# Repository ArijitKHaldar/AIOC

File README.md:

# AIOC-BMT

This is the Ham Radio _All-in-one-Cable_ with a USB Type-A instead of USB-C which is inspired from [AIOC](https://github.com/skuep/AIOC). **It is currently not tested, and is still a proof of concept only!** Please read this README carefully before ordering anything.

## What does it do?

The AIOC-BMT is a small adapter with a USB-A connector that enumerates itself as a sound-card (e.g. for APRS purposes), a virtual tty ("COM Port") for programming and asserting the PTT (Push-To-Talk) as well as a CM108 compatible HID endpoint for CM108-style PTT (new in firmware version 1.2.0).

## Features

- Cheap & Hackable Digital mode USB interface (similar to digirig, mobilinkd, etc...)
- Programming Cable Function via virtual Serial Port
- Compact form-factor (DIY overmolded enclosure is currently TBD)
- Based on easy-to-hack **STM32F302** with internal ADC/DAC (Programmable via USB bootloader using [DFU](#how-to-program))
- Can support Dual-PTT HTs
- Supports all popular OSes (Linux, Windows and MacOS with limitations[\*](https://github.com/skuep/AIOC/issues/13))

## Compatibility

### Software

- [Direwolf](#notes-on-direwolf) as AX.25 modem/APRS en+decoder/...
- [AllStarLink](#notes-on-allstarlink-asl3) as ASL Node
- [APRSdroid](#notes-on-aprsdroid) as APRS en+decoder
- [CHIRP](#notes-on-chirp) for programming
- [VaraFM](#notes-on-varafm)
- ... and more

### Tested Radios (so far)

TODO

## How To Fab

- Go to JLCPCB.com and upload the AIOC-BMT.zip package (under `aioc-bmt\production`)
  - Select PCB Thickness 1.6mm (you can select any thickness of your choice, as long as the USB connector can be mounted)
  - You may want to select LeadFree HASL
  - Select Silkscreen/Soldermask color to your liking
  - Choose Mark on PCB: Order Number(Specify Position)
- Check "PCB Assembly"
  - PCBA Type "Economic"
  - Assembly Side "Top Side"
  - Tooling Holes "Added by Customer"
  - Press Confirm
  - Click "Add BOM File" and upload `bom.csv`
  - Click "Add CPL File" and upload `positions.csv`
  - Press Next
  - Look Through components, see if something is missing or problematic and press Next
  - Check everything looks roughly good (rotations are already baked-in and should be correct). Save to Cart

This gives you 5 (or more) SMD assembled AIOC-BMT. The only thing left to do is soldering on the audio cables.
You can choose to fabricate 5 PCBs, but populate 2, which will reduce the cost, but you have to solder the rest of the boards yourself in that case.

**Note** that the following message from JLCPCB is okay and can be ignored.

```
The below parts won't be assembled due to data missing.
J1,J2,J3,J4 designators don't exist in the BOM file.
```

**Note** for people doing their own PCB production: I suggest using the LCSC part numbers in the BOM file as a guide on what to buy (especially regarding the MCU).

## How To Build

For building the firmware, clone the repository and initialize the submodules. Create an empty workspace with the STM32CubeIDE and import the project.

- `git clone <repositry url>`
- `git submodule update --init`
- Start STM32CubeIDE and create a new workspace under `<project-root>/stm32`
- Choose File->Import and import the `aioc-fw` project in the same folder without copying
- Select Project->Build All and the project should build. Use the Release build unless you specifically want to debug an issue

## How To Program

### Initial programming

The following steps are required for initial programming of the AIOC-BMT:

- Short outermost pins on the programming header. This will set the device into bootloader mode in the next step.
  
- Connect USB-A cable to the AIOC-BMT PCB
- Use a tool like `dfu-util` to program the firmware binary from the GitHub Releases page like this:
  ```
  dfu-util -a 0 -s 0x08000000:leave -D aioc-fw-x-y-z.bin
  ```
  **Note** that a `libusb` driver is required for this. On Windows there are additional steps required as shown [here](https://yeswolf.github.io/dfu) (_DFuSe Utility and dfu-util_). On other operating systems (e.g. Linux, MacOS), this just works ™ (provided libusb is installed on your system).
  On Linux (and MacOS), your user either needs to have the permission to use libusb (`plugdev` group) or you might need to use `sudo`.
- Remove short from first step, unplug and replug the device, it should now enumerate as the AIOC-BMT device

### Firmware updating

Once the AIOC-BMT has firmware loaded onto it, it can be re-programmed without the above BOOT sequence by following these steps.

**Note** This requires firmware version >= 1.2.0. For older firmwares, the initial programming sequence above is required for updating the firmware.

- Run `dfu-util` like this
  ```
  dfu-util -d 1209:7388 -a 0 -s 0x08000000:leave -D aioc-fw-x-y-z.bin
  ```

This will reboot the AIOC-BMT into the bootloader automatically and perform the programming.
After that, it automatically reboots the AIOC-BMT into the newly programmed firmware.

**Note** Should you find yourself with a bricked AIOC-BMT, use the initial programming sequence above

## How To Use

The serial interface of the AIOC-BMT enumerates as a regular COM (Windows) or ttyACM port (Linux) and can be used as such for programming the radio as well as PTT (Asserted on `DTR=1` and `RTS=0`).

**Note** before firmware version 1.2.0, PTT was asserted by `DTR=1` (ignoring RTS) which caused problems with certain radios when using the serial port for programming the radio e.g. using CHIRP.

The soundcard interface of the AIOC-BMT gives access to the audio data channels. It has one mono microphone channel and one mono speaker channel and currently supports the following baudrates:

- 48000 Hz (preferred)
- 32000 Hz
- 24000 Hz
- 22050 Hz (specifically for APRSdroid, has approx. 90 ppm of frequency error)
- 16000 Hz
- 12000 Hz
- 11025 Hz (has approx. 90 ppm of frequency error)
- 8000 Hz

Since firmware version 1.2.0, a CM108 style PTT interface is available for public testing. This interface works in parallel to the COM-port PTT.
Direwolf on Linux is confirmed working, please report any issues. Note that currently, Direwolf reports some warnings when using the CM108 PTT interface on the AIOC.
While they are annoying, they are safe to ignore and require changes in the upstream direwolf sourcecode. See https://github.com/wb2osz/direwolf/issues/448 for more details.

## Notes on Direwolf

- Follow the regular setup guide with [Direwolf](https://github.com/wb2osz/direwolf) to determine the correct audio device to use.
  For the serial and CM108 PTT interfaces on Linux, you need to set correct permissions on the ttyACM/hidraw devices. Consult Direwolf manual.
- Configure the device as follows
  ```
  [...]
  ADEVICE plughw:<x>,0  # <- Linux
  ADEVICE x 0           # <- Windows
  ARATE 48000
  [...]
  PTT CM108             # <- Use the new CM108 compatible style PTT interface
  PTT <port> DTR -RTS   # <- Alternatively use an old school serial device for PTT
  [...]
  ```

## Notes on AllStarLink (ASL3)

Once your cable is emulating a CM108, it becomes quite simple to plug into your HT and setup a simple simplex AllStarLink node that talks to your favorite repeater or node.

In `asl-menu`, set:

- Device type: `usbradio` (menu sections: 2 > A1 > N4 > I2)
- Duplex type: `1` (menu sections: 2 > A1 > N5)

Edit `usbradio.conf` (menu sections: 6 > H) (for a Puxing PX-888 cheap Chineese HT)

- `rxboost = 0`
- `rxsqhyst = 500`
- `carrierfrom = usbinvert`
- `ctcssfrom = no`
- `rxdemod = speaker`
- `txprelim = no`
- `invertptt = no`

## Notes on APRSdroid

[APRSdroid](https://aprsdroid.org/) support has been added by AIOC by implementing support for the fixed 22050 Hz sample rate that APRSdroid requires.
It is important to notice, that the exact sample rate can not be achieved by the hardware, due to the 8 MHz crystal.
The actual sample rate used is 22052 Hz (which represents around 90 ppm of error). From my testing this does not seem to be a problem for APRS at all.

However, since APRSdroid does not have any PTT control, sending data is currently not possible using the AIOC except using the radio VOX function. See https://github.com/ge0rg/aprsdroid/issues/324.
My previous experience is, that the Android kernel brings support for ttyACM devices (which is perfect for the AIOC) so implementing this feature for APRSdroid should theoretically be no problem.

Ideas such as implementing a digital-modes-spefic VOX-emulation to workaround this problem and let the AIOC activate the PTT automatically are currently being considered.
Voice your opinion and ideas in the GitHub issues if this seems interesting to you.

## Notes on CHIRP

CHIRP is a very popuplar open-source programming software that supports a very wide array of HT radios. You can use CHIRP just as you would like with a regular programming cable.

Download:

- Start CHIRP
- Select Radio->Download from Radio
- Select the AIOC COM/ttyACM port and start

Upload:

- Select Radio->Upload to Radio
- That's it

## Notes on VaraFM

Select "DTR only" for PTT Pin, so that the correct RTS/DTR sequence is generated for PTT

# Known issues

TODO

# Future work

TODO

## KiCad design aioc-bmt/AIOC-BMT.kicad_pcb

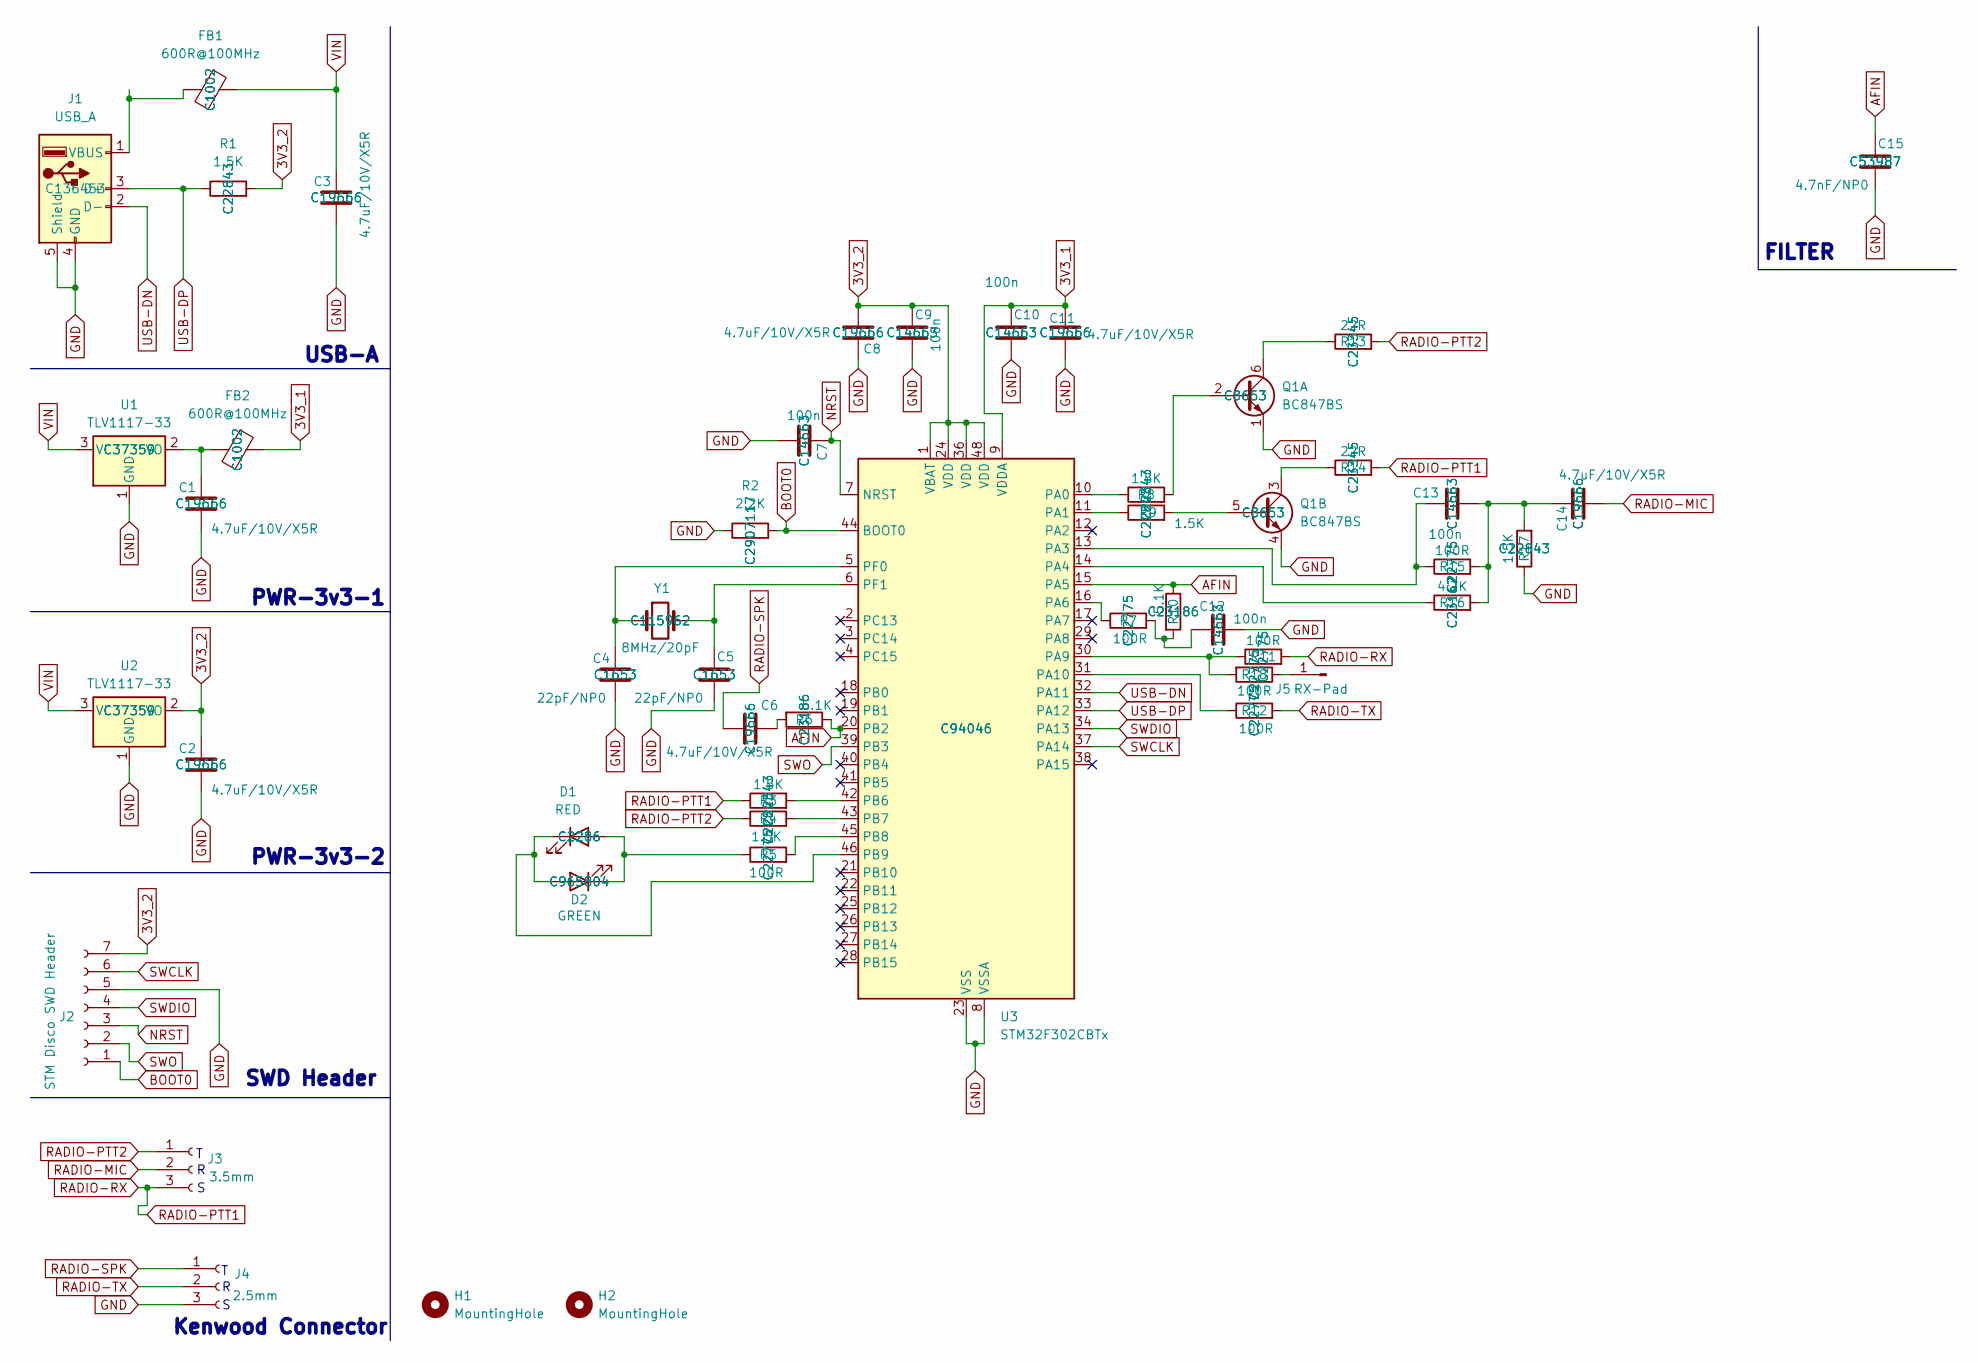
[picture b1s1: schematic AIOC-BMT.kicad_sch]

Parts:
C1, C2, C3, C6, C8, C11, C14: 4.7uF/10V/X5R; C_0603_1608Metric_Pad1.08x0.95mm_HandSolder; MPN C19666; LCSC Part# C19666
C4, C5: 22pF/NP0; C_0603_1608Metric_Pad1.08x0.95mm_HandSolder; MPN C1653; LCSC Part# C1653
C7, C9, C10, C12, C13: 100n; C_0603_1608Metric_Pad1.08x0.95mm_HandSolder; MPN C14663; LCSC Part# C14663
C15: 4.7nF/NP0; C_0603_1608Metric_Pad1.08x0.95mm_HandSolder; MPN C53987; LCSC Part# C53987
D1: RED; LED_0603_1608Metric_Pad1.05x0.95mm_HandSolder; MPN C2286; LCSC Part# C2286
D2: GREEN; LED_0603_1608Metric_Pad1.05x0.95mm_HandSolder; MPN C965804; LCSC Part# C965804
FB1, FB2: 600R@100MHz; L_0603_1608Metric_Pad1.05x0.95mm_HandSolder; MPN C1002; LCSC Part# C1002
H1, H2: MountingHole; ToolingHole_1.152mm
J1: USB_A; USB_A_Molex_48037-2200_Horizontal; MPN C136453; LCSC Part# C136453
J2: STM Disco SWD Header; PinSocket_1x07_P2.54mm_Vertical
J3: 3.5mm; PinSocket_1x03_P2.54mm_Vertical
J4: 2.5mm; PinSocket_1x03_P2.54mm_Vertical
J5: RX-Pad; TestPoint_Pad_2.5x2.5mm
Q1: BC847BS; SOT-363_SC-70-6; MPN C8653; LCSC Part# C8653
R1, R3, R4, R8, R9, R17: 1.5K; R_0603_1608Metric_Pad0.98x0.95mm_HandSolder; MPN C22843; LCSC Part# C22843
R2: 2.2K; R_0603_1608Metric_Pad0.98x0.95mm_HandSolder; MPN C2907117; LCSC Part# C2907117
R5, R7, R11, R12, R15, R18: 100R; R_0603_1608Metric_Pad0.98x0.95mm_HandSolder; MPN C22775; LCSC Part# C22775
R6, R10: 5.1K; R_0603_1608Metric_Pad0.98x0.95mm_HandSolder; MPN C23186; LCSC Part# C23186
R13, R14: 22R; R_0603_1608Metric_Pad0.98x0.95mm_HandSolder; MPN C23345; LCSC Part# C23345
R16: 4.7K; R_0603_1608Metric_Pad0.98x0.95mm_HandSolder; MPN C23162; LCSC Part# C23162
U1, U2: TLV1117-33; SOT-223-3_TabPin2; MPN C37359; LCSC Part# C37359
U3: STM32F302CBTx; LQFP-48_7x7mm_P0.5mm; MPN C94046; LCSC Part# C94046
Y1: 8MHz/20pF; Crystal_SMD_5032-2Pin_5.0x3.2mm_HandSoldering; MPN C115962; LCSC Part# C115962

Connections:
3V3_1: C10.1, C11.2, FB2.1, U3.9 (VDDA)
3V3_2: C2.1, C8.2, C9.1, J2.7, R1.2, U2.2 (VO), U3.1 (VBAT), U3.24 (VDD), U3.36 (VDD), U3.48 (VDD)
AFIN: C15.1, R6.1, R10.1, U3.15 (PA5), U3.20 (PB2)
BOOT0: J2.1, R2.2, U3.44 (BOOT0)
GND: C1.2, C2.2, C3.2, C4.2, C5.2, C7.2, C8.1, C9.2, C10.2, C11.1, C12.1, C15.2, J1.4 (GND), J1.5 (Shield), J2.5, J4.3, Q1.1 (E1), Q1.4 (E2), R2.1, R17.1, U1.1 (GND), U2.1 (GND), U3.8 (VSSA), U3.23 (VSS), U3.35 (VSS), U3.47 (VSS)
NRST: C7.1, J2.3, U3.7 (NRST)
unnamed: C6.2, R6.2
unnamed: C12.2, R7.2, R10.2
unnamed: C13.2, C14.1, R15.2, R16.2, R17.2
unnamed: D1.2 (A), D2.1 (K), R5.1
unnamed: D1.1 (K), D2.2 (A), U3.46 (PB9)
unnamed: FB1.2, J1.1 (VBUS)
unnamed: J5.1, R18.1
unnamed: Q1.2 (B1), R8.2
unnamed: Q1.6 (C1), R13.1
unnamed: Q1.5 (B2), R9.2
unnamed: Q1.3 (C2), R14.1
unnamed: C1.1, FB2.2, U1.2 (VO)
unnamed: R8.1, U3.10 (PA0)
unnamed: R9.1, U3.11 (PA1)
unnamed: C13.1, R15.1, U3.13 (PA3)
unnamed: R16.1, U3.14 (PA4)
unnamed: R7.1, U3.16 (PA6)
unnamed: R11.1, R18.2, U3.30 (PA9)
unnamed: R12.1, U3.31 (PA10)
unnamed: R3.2, U3.42 (PB6)
unnamed: R4.2, U3.43 (PB7)
unnamed: R5.2, U3.45 (PB8)
unnamed: C4.1, U3.5 (PF0), Y1.1
unnamed: C5.1, U3.6 (PF1), Y1.2
RADIO-MIC: C14.2, J3.2
RADIO-PTT1: J3.3, R3.1, R11.2, R14.2
RADIO-PTT2: J3.1, R4.1, R13.2
RADIO-SPK: C6.1, J4.1
RADIO-TX: J4.2, R12.2
SWCLK: J2.6, U3.37 (PA14)
SWDIO: J2.4, U3.34 (PA13)
SWO: J2.2, U3.39 (PB3)
USB-DN: J1.2 (D-), U3.32 (PA11)
USB-DP: J1.3 (D+), R1.1, U3.33 (PA12)
VIN: C3.1, FB1.1, U1.3 (VI), U2.3 (VI)

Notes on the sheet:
SWD Header
USB-A
PWR-3v3-1
PWR-3v3-2
Kenwood Connector
FILTER

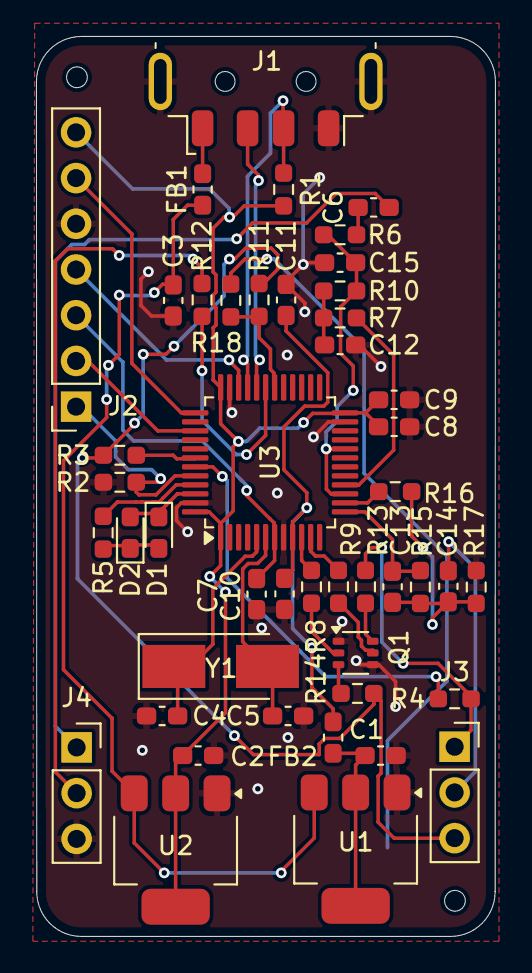
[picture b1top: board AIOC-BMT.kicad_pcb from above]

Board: 2 copper layers, 25.5 x 50.0 mm, 49 parts (1 on the bottom side), 41 nets.

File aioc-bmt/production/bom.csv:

Designator,Footprint,Quantity,Value,LCSC Part #
"C1, C11, C14, C2, C3, C6, C8",0603,7,4.7uF/10V/X5R,C19666
"C10, C12, C13, C7, C9",0603,5,100n,C14663
C15,0603,1,4.7nF/NP0,C53987
"C4, C5",0603,2,22pF/NP0,C1653
D1,0603,1,RED,C2286
D2,0603,1,GREEN,C965804
"FB1, FB2",0603,2,600R@100MHz,C1002
Q1,SOT-363_SC-70-6,1,BC847BS,C8653
"R1, R17, R3, R4, R8, R9",0603,6,1.5K,C22843
"R10, R6",0603,2,5.1K,C23186
"R11, R12, R15, R18, R5, R7",0603,6,100R,C22775
"R13, R14",0603,2,22R,C23345
R16,0603,1,4.7K,C23162
R2,0603,1,2.2K,C2907117
"U1, U2",SOT-223-3_TabPin2,2,TLV1117-33,C37359
U3,LQFP-48_7x7mm_P0.5mm,1,STM32F302CBTx,C94046
Y1,Crystal_SMD_5032-2Pin_5.0x3.2mm_HandSoldering,1,8MHz/20pF,C115962

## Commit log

2025-03-22 Add files for AIOC-BMT
